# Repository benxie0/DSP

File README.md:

# DSP
SSM3302ACPZ

ADAU1701JSTZ

LT3045EMSE-1#PBF

SSM2306CPZ-REEL7

CAT24C16WI-GT3 OR M24C64-DRDW8TP/K

ZX5T953GTA

_____________________________________

TDA7491HVU13TR

TDA7491HV13TR

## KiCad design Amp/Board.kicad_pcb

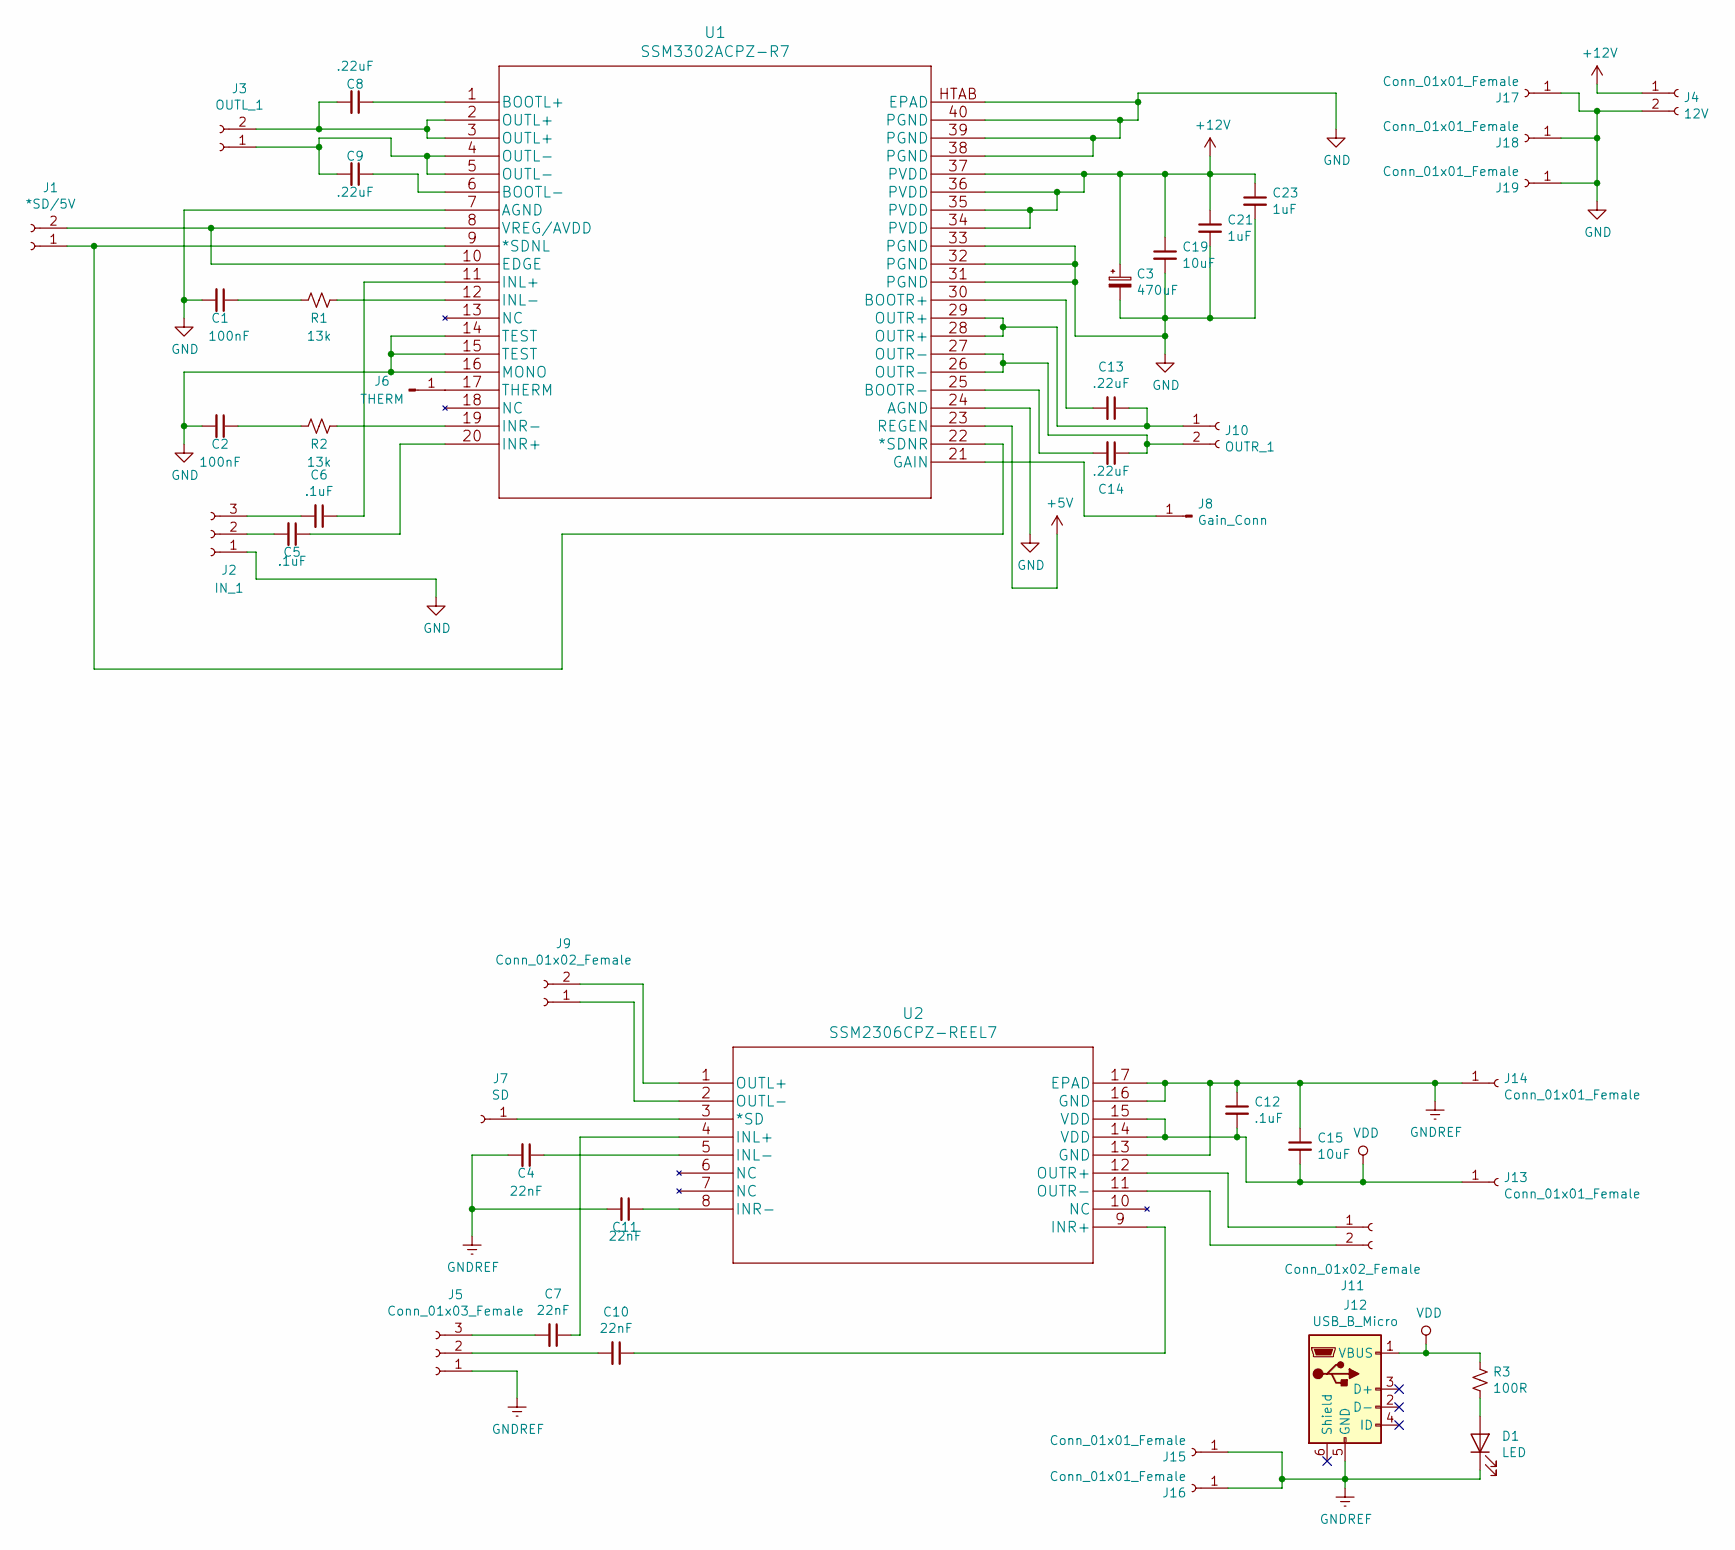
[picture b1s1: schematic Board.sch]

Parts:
C1, C2: 100nF; C_0805_2012Metric_Pad1.15x1.40mm_HandSolder
C3: 470uF; CP_Radial_D8.0mm_P3.50mm
C4, C7, C10, C11: 22nF; C_0805_2012Metric_Pad1.15x1.40mm_HandSolder
C5, C6, C12: .1uF; C_0805_2012Metric_Pad1.15x1.40mm_HandSolder
C8, C9, C13, C14: .22uF; C_0805_2012Metric_Pad1.15x1.40mm_HandSolder
C15, C19: 10uF; C_0805_2012Metric_Pad1.15x1.40mm_HandSolder
C21, C23: 1uF; C_0805_2012Metric_Pad1.15x1.40mm_HandSolder
D1: LED; LED_0805_2012Metric_Pad1.15x1.40mm_HandSolder
J1: *SD/5V; PinHeader_1x02_P2.54mm_Vertical
J2: IN_1; 691213710003
J3: OUTL_1; WJ250A3502P
J4: 12V; WJ250A3502P
J5: Conn_01x03_Female; 691213710003
J6: THERM; PinHeader_1x01_P2.54mm_Vertical
J7: SD; PinHeader_1x01_P2.54mm_Vertical
J8: Gain_Conn; PinHeader_1x01_P2.54mm_Vertical
J9, J11: Conn_01x02_Female; WJ250A3502P
J10: OUTR_1; WJ250A3502P
J12: USB_B_Micro; C77238
J13, J14: Conn_01x01_Female; PinHeader_1x01_P2.54mm_Vertical
J15, J16, J17, J18, J19: Conn_01x01_Female; MountingHole_3.2mm_M3_ISO7380_Pad
R1, R2: 13k; R_0805_2012Metric_Pad1.15x1.40mm_HandSolder
R3: 100R; R_0805_2012Metric_Pad1.15x1.40mm_HandSolder
U1: SSM3302ACPZ-R7
U2: SSM2306CPZ-REEL7

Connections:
+5V: U1.23 (REGEN)
+12V: C3.1, C19.1, C21.1, C23.1, J4.1, U1.34 (PVDD), U1.35 (PVDD), U1.36 (PVDD), U1.37 (PVDD)
GND: C1.2, C2.2, C3.2, C19.2, C21.2, C23.2, J2.1, J4.2, J17.1, J18.1, J19.1, U1.7 (AGND), U1.14 (TEST), U1.15 (TEST), U1.16 (MONO), U1.24 (AGND), U1.31 (PGND), U1.32 (PGND), U1.33 (PGND), U1.38 (PGND), U1.39 (PGND), U1.40 (PGND), U1.HTAB (EPAD)
GNDREF: C4.2, C11.2, C12.1, C15.1, D1.1 (K), J5.1, J12.5 (GND), J14.1, J15.1, J16.1, U2.13 (GND), U2.16 (GND), U2.17 (EPAD)
unnamed: C1.1, R1.2
unnamed: C2.1, R2.2
unnamed: C4.1, U2.5 (INL-)
unnamed: C5.1, U1.20 (INR+)
unnamed: C5.2, J2.2
unnamed: C6.1, U1.11 (INL+)
unnamed: C6.2, J2.3
unnamed: C7.1, U2.4 (INL+)
unnamed: C7.2, J5.3
unnamed: C8.1, U1.1 (BOOTL+)
unnamed: C8.2, J3.2, U1.2 (OUTL+), U1.3 (OUTL+)
unnamed: C9.1, U1.6 (BOOTL-)
unnamed: C9.2, J3.1, U1.4 (OUTL-), U1.5 (OUTL-)
unnamed: C10.1, U2.9 (INR+)
unnamed: C10.2, J5.2
unnamed: C11.1, U2.8 (INR-)
unnamed: C13.1, J10.1, U1.28 (OUTR+), U1.29 (OUTR+)
unnamed: C13.2, U1.30 (BOOTR+)
unnamed: C14.1, J10.2, U1.26 (OUTR-), U1.27 (OUTR-)
unnamed: C14.2, U1.25 (BOOTR-)
unnamed: D1.2 (A), R3.2
unnamed: J1.1, U1.9 (*SDNL), U1.22 (*SDNR)
unnamed: J1.2, U1.8 (VREG/AVDD), U1.10 (EDGE)
unnamed: J6.1, U1.17 (THERM)
unnamed: J7.1, U2.3 (*SD)
unnamed: J8.1, U1.21 (GAIN)
unnamed: J9.1, U2.2 (OUTL-)
unnamed: J9.2, U2.1 (OUTL+)
unnamed: J11.1, U2.12 (OUTR+)
unnamed: J11.2, U2.11 (OUTR-)
unnamed: R1.1, U1.12 (INL-)
unnamed: R2.1, U1.19 (INR-)
VDD: C12.2, C15.2, J12.1 (VBUS), J13.1, R3.1, U2.14 (VDD), U2.15 (VDD)

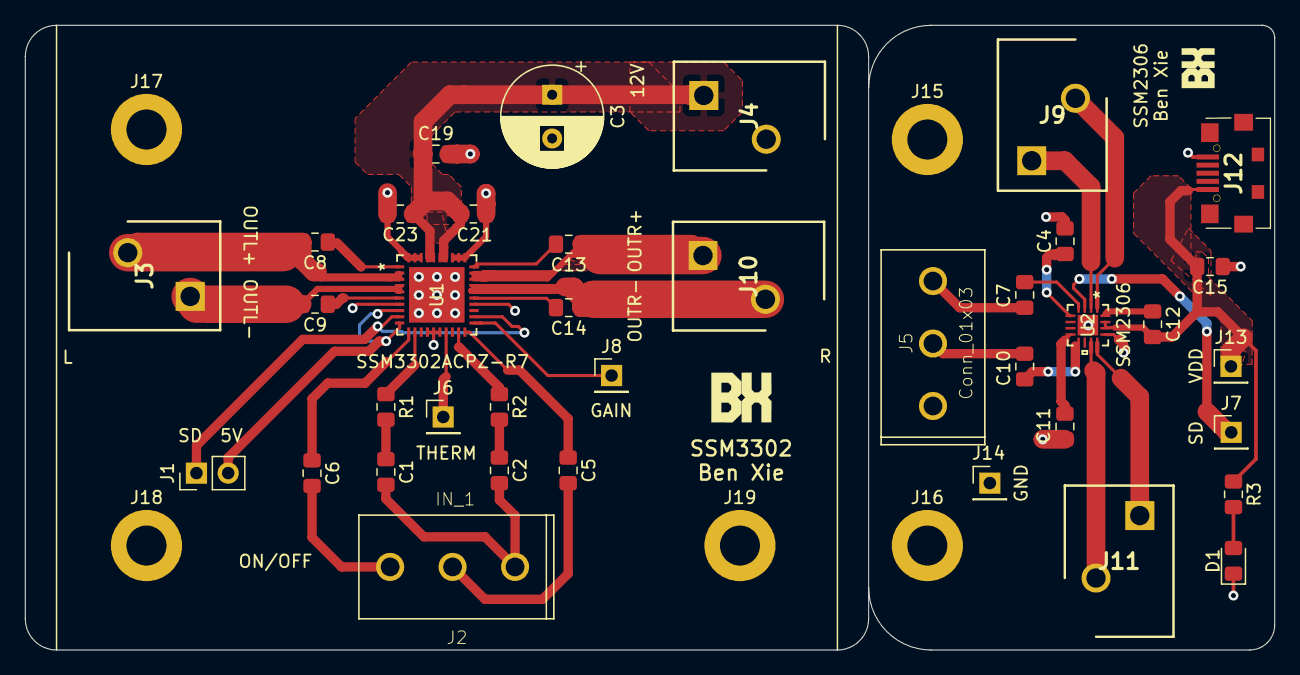
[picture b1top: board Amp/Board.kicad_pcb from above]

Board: 2 copper layers, 100.0 x 50.0 mm, 43 parts (0 on the bottom side), 36 nets.

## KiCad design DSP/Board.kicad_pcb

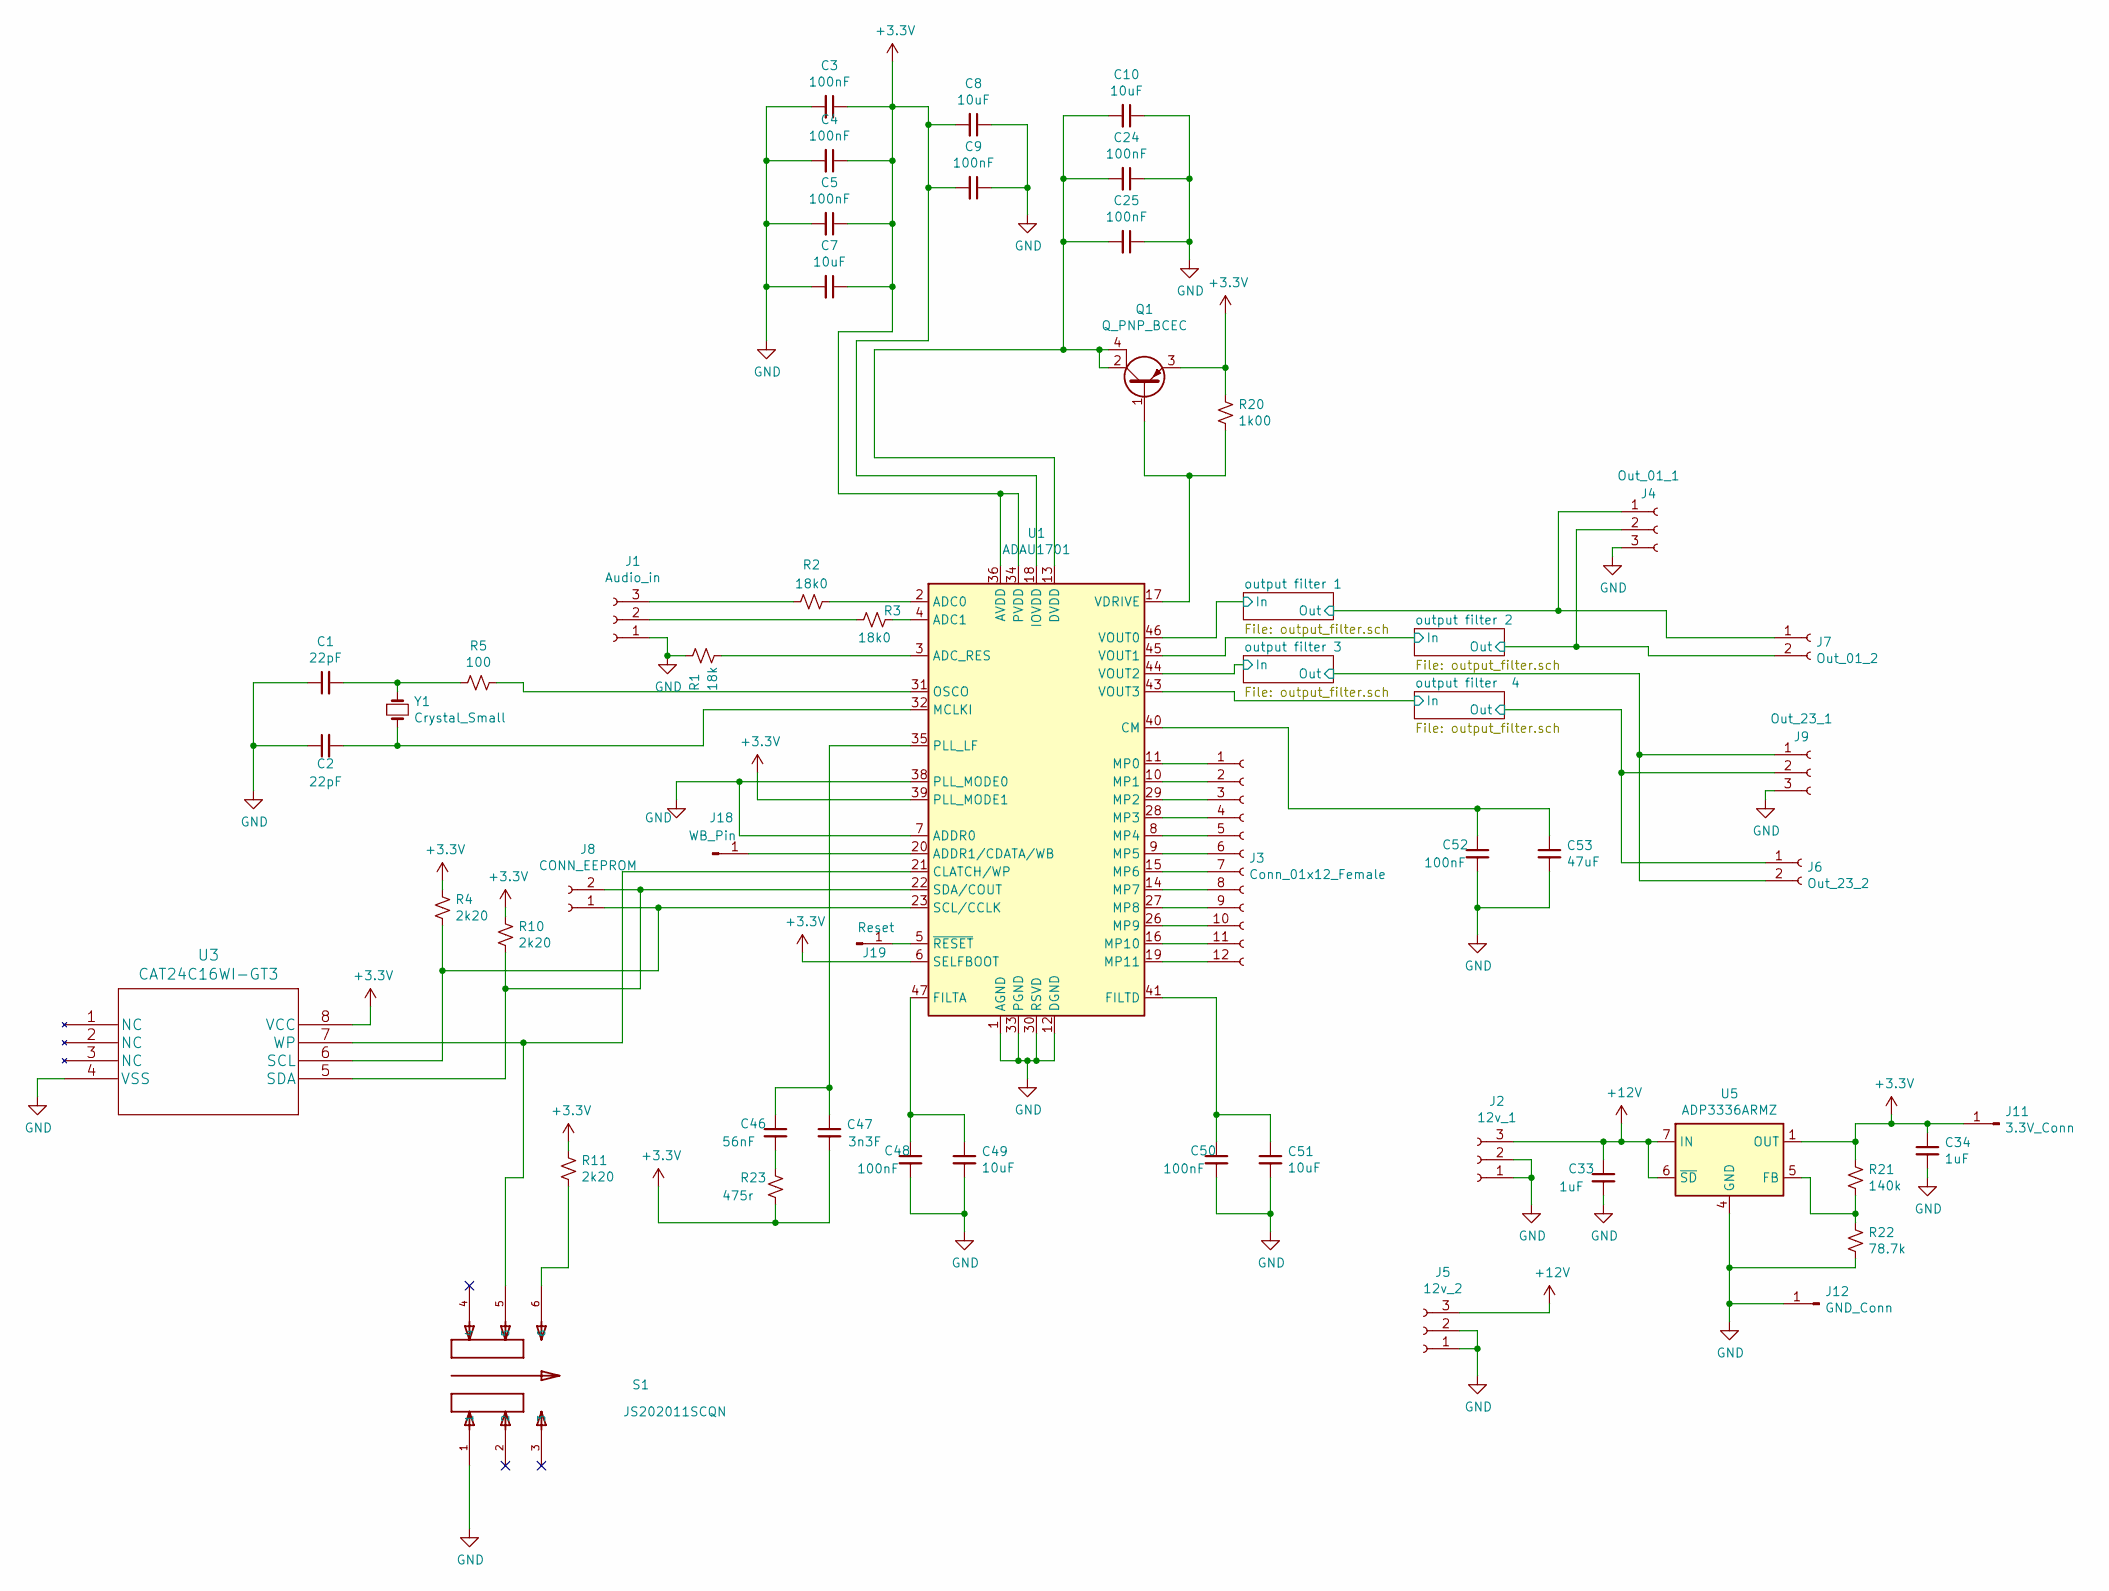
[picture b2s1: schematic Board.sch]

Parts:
C1, C2: 22pF; C_0805_2012Metric_Pad1.15x1.40mm_HandSolder
C3, C4, C5, C9, C24, C25, C48, C50, C52: 100nF; C_0805_2012Metric_Pad1.15x1.40mm_HandSolder
C7, C8, C10, C49, C51: 10uF; C_0805_2012Metric_Pad1.15x1.40mm_HandSolder
C33, C34: 1uF; C_0805_2012Metric_Pad1.15x1.40mm_HandSolder
C46: 56nF; C_0805_2012Metric_Pad1.15x1.40mm_HandSolder
C47: 3n3F; C_0805_2012Metric_Pad1.15x1.40mm_HandSolder
C53: 47uF; C_0805_2012Metric_Pad1.15x1.40mm_HandSolder
J1: Audio_in; 691213710003
J2: 12v_1; 691213710003
J3: Conn_01x12_Female; PinHeader_1x12_P2.54mm_Vertical
J4: Out_01_1; 691213710003
J5: 12v_2; 691213710003
J6: Out_23_2; WJ250A3502P
J7: Out_01_2; WJ250A3502P
J8: CONN_EEPROM; PinHeader_1x02_P2.54mm_Vertical
J9: Out_23_1; 691213710003
J11: 3.3V_Conn; PinHeader_1x01_P2.54mm_Vertical
J12: GND_Conn; PinHeader_1x01_P2.54mm_Vertical
J18: WB_Pin; PinHeader_1x01_P2.54mm_Vertical
J19: Reset; PinHeader_1x01_P2.54mm_Vertical
Q1: Q_PNP_BCEC; SOT-223
R1: 18k; R_0805_2012Metric_Pad1.15x1.40mm_HandSolder
R2, R3: 18k0; R_0805_2012Metric_Pad1.15x1.40mm_HandSolder
R4, R10, R11: 2k20; R_0805_2012Metric_Pad1.15x1.40mm_HandSolder
R5: 100; R_0805_2012Metric_Pad1.15x1.40mm_HandSolder
R20: 1k00; R_0805_2012Metric_Pad1.15x1.40mm_HandSolder
R21: 140k; R_0805_2012Metric_Pad1.15x1.40mm_HandSolder
R22: 78.7k; R_0805_2012Metric_Pad1.15x1.40mm_HandSolder
R23: 475r; R_0805_2012Metric_Pad1.15x1.40mm_HandSolder
S1: JS202011SCQN; SW_JS202011SCQN
U1: ADAU1701; LQFP-48_7x7mm_P0.5mm
U3: CAT24C16WI-GT3
U5: ADP3336ARMZ; MSOP-8_3x3mm_P0.65mm
Y1: Crystal_Small; OSCCC500X320X135

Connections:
+3V3: C3.1, C4.1, C5.1, C7.1, C8.2, C9.2, C34.1, C47.2, J11.1, Q1.3 (E), R4.1, R10.1, R11.1, R20.1, R21.1, R23.2, U1.6 (SELFBOOT), U1.18 (IOVDD), U1.34 (PVDD), U1.36 (AVDD), U1.39 (PLL_MODE1), U1.48 (AVDD), U3.8 (VCC), U5.1 (OUT), U5.2 (OUT), U5.3 (OUT)
+12V: C33.1, J2.3, J5.3, U5.6 (~SD), U5.7 (IN), U5.8 (IN)
/output filter 1/In: U1.46 (VOUT0); also elsewhere on the board
/output filter 1/Out: J4.1, J7.1; also elsewhere on the board
/output filter 2/In: U1.45 (VOUT1); also elsewhere on the board
/output filter 2/Out: J4.2, J7.2; also elsewhere on the board
/output filter 3/In: U1.44 (VOUT2); also elsewhere on the board
/output filter 3/Out: J6.2, J9.1; also elsewhere on the board
/output filter 4/In: U1.43 (VOUT3); also elsewhere on the board
/output filter 4/Out: J6.1, J9.2; also elsewhere on the board
GND: C1.1, C2.1, C3.2, C4.2, C5.2, C7.2, C8.1, C9.1, C10.1, C24.1, C25.1, C33.2, C34.2, C48.2, C49.2, C50.2, C51.2, C52.2, C53.2, J1.1, J2.1, J2.2, J4.3, J5.1, J5.2, J9.3, J12.1, R1.1, R22.2, S1.1, U1.1 (AGND), U1.7 (ADDR0), U1.12 (DGND), U1.25 (DGND), U1.30 (RSVD), U1.33 (PGND), U1.37 (AGND), U1.38 (PLL_MODE0), U1.42 (AGND), U3.4 (VSS), U5.4 (GND); also elsewhere on the board
unnamed: C1.2, R5.2, Y1.1
unnamed: C2.2, U1.32 (MCLKI), Y1.2
unnamed: C10.2, C24.2, C25.2, Q1.2 (C), Q1.4 (C), U1.13 (DVDD), U1.24 (DVDD)
unnamed: C46.1, C47.1, U1.35 (PLL_LF)
unnamed: C46.2, R23.1
unnamed: C48.1, C49.1, U1.47 (FILTA)
unnamed: C50.1, C51.1, U1.41 (FILTD)
unnamed: C52.1, C53.1, U1.40 (CM)
unnamed: J1.2, R3.2
unnamed: J1.3, R2.2
unnamed: J3.1, U1.11 (MP0)
unnamed: J3.2, U1.10 (MP1)
unnamed: J3.3, U1.29 (MP2)
unnamed: J3.4, U1.28 (MP3)
unnamed: J3.5, U1.8 (MP4)
unnamed: J3.6, U1.9 (MP5)
unnamed: J3.7, U1.15 (MP6)
unnamed: J3.8, U1.14 (MP7)
unnamed: J3.9, U1.27 (MP8)
unnamed: J3.10, U1.26 (MP9)
unnamed: J3.11, U1.16 (MP10)
unnamed: J3.12, U1.19 (MP11)
unnamed: J8.1, R4.2, U1.23 (SCL/CCLK), U3.6 (SCL)
unnamed: J8.2, R10.2, U1.22 (SDA/COUT), U3.5 (SDA)
unnamed: J18.1, U1.20 (ADDR1/CDATA/WB)
unnamed: J19.1, U1.5 (~RESET)
unnamed: Q1.1 (B), R20.2, U1.17 (VDRIVE)
unnamed: R1.2, U1.3 (ADC_RES)
unnamed: R2.1, U1.2 (ADC0)
unnamed: R3.1, U1.4 (ADC1)
unnamed: R5.1, U1.31 (OSCO)
unnamed: R11.2, S1.6
unnamed: R21.2, R22.1, U5.5 (FB)
unnamed: S1.5, U1.21 (CLATCH/WP), U3.7 (WP)

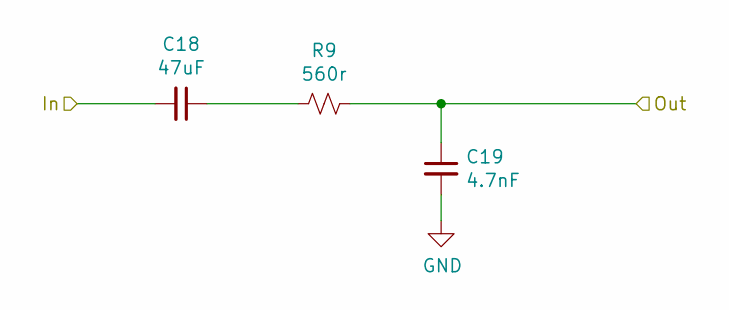
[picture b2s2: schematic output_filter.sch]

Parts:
C12: 47uF; C_0805_2012Metric_Pad1.15x1.40mm_HandSolder
C13: 4.7nF; C_0805_2012Metric_Pad1.15x1.40mm_HandSolder
R6: 560r; R_0805_2012Metric_Pad1.15x1.40mm_HandSolder

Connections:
/output filter 2/In: C12.2; also elsewhere on the board
GND: C13.2; also elsewhere on the board
unnamed 15: C13.1, R6.1; also elsewhere on the board
unnamed: C12.1, R6.2

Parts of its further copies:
C14, C16, C18: 47uF; C_0805_2012Metric_Pad1.15x1.40mm_HandSolder
C15, C17, C19: 4.7nF; C_0805_2012Metric_Pad1.15x1.40mm_HandSolder
R7, R8, R9: 560r; R_0805_2012Metric_Pad1.15x1.40mm_HandSolder

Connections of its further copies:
/output filter 1/In: C14.2; also elsewhere on the board
/output filter 3/In: C16.2; also elsewhere on the board
/output filter 4/In: C18.2; also elsewhere on the board
GND: C15.2, C17.2, C19.2; also elsewhere on the board
unnamed: C14.1, R7.2
unnamed 18: C15.1, R7.1; also elsewhere on the board
unnamed: C16.1, R8.2
unnamed 20: C17.1, R8.1; also elsewhere on the board
unnamed: C18.1, R9.2
unnamed 22: C19.1, R9.1; also elsewhere on the board

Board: 2 copper layers, 71 parts (0 on the bottom side), 57 nets, no tracks yet.

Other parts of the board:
C11, C26, C27, C28: 100nF; C_0805_2012Metric_Pad1.15x1.40mm_HandSolder
R12, R13, R14, R15: 13k; R_0805_2012Metric_Pad1.15x1.40mm_HandSolder

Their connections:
/output filter 1/Out: R13.1; also elsewhere on the board
/output filter 2/Out: R12.1; also elsewhere on the board
/output filter 3/Out: R14.1; also elsewhere on the board
/output filter 4/Out: R15.1; also elsewhere on the board
unnamed: C11.1, R12.2
unnamed 15: C11.2; also elsewhere on the board
unnamed 18: C26.2; also elsewhere on the board
unnamed 20: C27.2; also elsewhere on the board
unnamed 22: C28.2; also elsewhere on the board
unnamed: C26.1, R13.2
unnamed: C27.1, R14.2
unnamed: C28.1, R15.2

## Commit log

2019-10-25 made project
2019-10-25 added chip footprints
2019-10-25 added all things
2019-10-25 added libraries
2019-11-15 finished setup
2019-11-15 fixed readme
2019-11-16 built power circuit
2019-11-16 added datasheets
2019-11-16 did some more stuff
2019-11-17 more improvements
2019-11-25 done
2019-11-28 split
2020-01-02 finished DSP and AMP

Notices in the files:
parts and their libraries:
Copyright 2016 Accelerated Designs. All rights reserved.
